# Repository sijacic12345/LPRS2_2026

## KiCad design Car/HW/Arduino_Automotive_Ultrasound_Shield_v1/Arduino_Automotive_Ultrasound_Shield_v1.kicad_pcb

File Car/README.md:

# 🏎️ ROS2 Robot Car

Robotski automobil baziran na **ROS2** platformi sa dualnom arhitekturom (SBC + MCU).

---

## 🏗️ Arhitektura sistema

Sistem koristi podelu poslova između Raspberry Pi 5 i Arduina radi maksimalne efikasnosti:

| Komponenta | Uloga | Opis |
| :--- | :--- | :--- |
| **Raspberry Pi 5** | **CPU (Master)** | Donosi odluke, obrađuje ROS2 čvorove i šalje instrukcije. |
| **Arduino Nano** | **Controller (Slave)** | Direktna kontrola BLDC motora, Servo motora i čitanje senzora. |

### 🛰️ Komunikacioni Protokol (`fw_pkgs.hpp`)
Komunikacija se vrši preko paketa definisanih u `fw_pkgs.hpp`. 
> [!CAUTION]
> **VAŽNO:** Ovaj fajl postoji na dve lokacije. Ako menjaš strukturu u jednom, **moraš** je promeniti u oba:
> 1. `FW/Arduino_Motoro_Controller` (za Arduino)
> 2. `ROS2/ackibot_ws/src/ackibot_node/src/` (za Raspberry Pi)

* **M2S (Master to Slave):** Komande sa Pi-ja ka Arduinu (motor, servo).
* **S2M (Slave to Master):** Telemetrija sa Arduina ka Pi-ju (senzori, status).

---

## 📂 Ključni Fajlovi

* **Firmware:** `FW/Arduino_Motor_Controller/Arduino_Motor_Controller.ino` (Učitati na Arduino)
* **ROS2 Node:** `ROS2/ackibot_ws/src/ackibot_node/src/fw_node.cpp` (Glavna logika instrukcija)

---

## 🚀 Procedura Pokretanja

Prati ove korake tačnim redosledom kako bi izbegao greške u komunikaciji:

1.  **Power On:** Uključi Raspberry Pi (Interni prekidač).
2.  **Access:** Poveži se na Pi putem **SSH**.
3.  **Scripts:** Pokreni skriptu za joypad
    ```bash
    cd ROS2/ackibot_ws/scripts
    ./mars_joys.sh
    ```
4.  **Controller:** Upali joypad kombinacijom tastera **RB + HOME**.
5.  **Run:** Pokreni glavni proces:
    ```bash
    ./ackibot_run_sbc.sh
    ```
6.  **Motors:** Na samom kraju uključi **eksterni prekidač** za motore.

---

## 📶 Troubleshooting (Wi-Fi Problemi)

Ako se Raspberry Pi ne vidi na mreži:
* Poveži PI na monitor i proveri IP adresu u konzoli.
* **Quick Fix:** Ako ne možeš da mu pristupiš, probaj da **pinguješ svoj PC sa Pi-ja**. To često natera ruter da prepozna uređaj i otvori rutu.

---

## 🛠️ Build Instructions
Detaljna uputstva za kompajliranje i build sistema možeš pronaći na:
👉 [GitHub Repository Build Guide](https://github.com/cxxx1828/ROS2-Robot-Car)

---

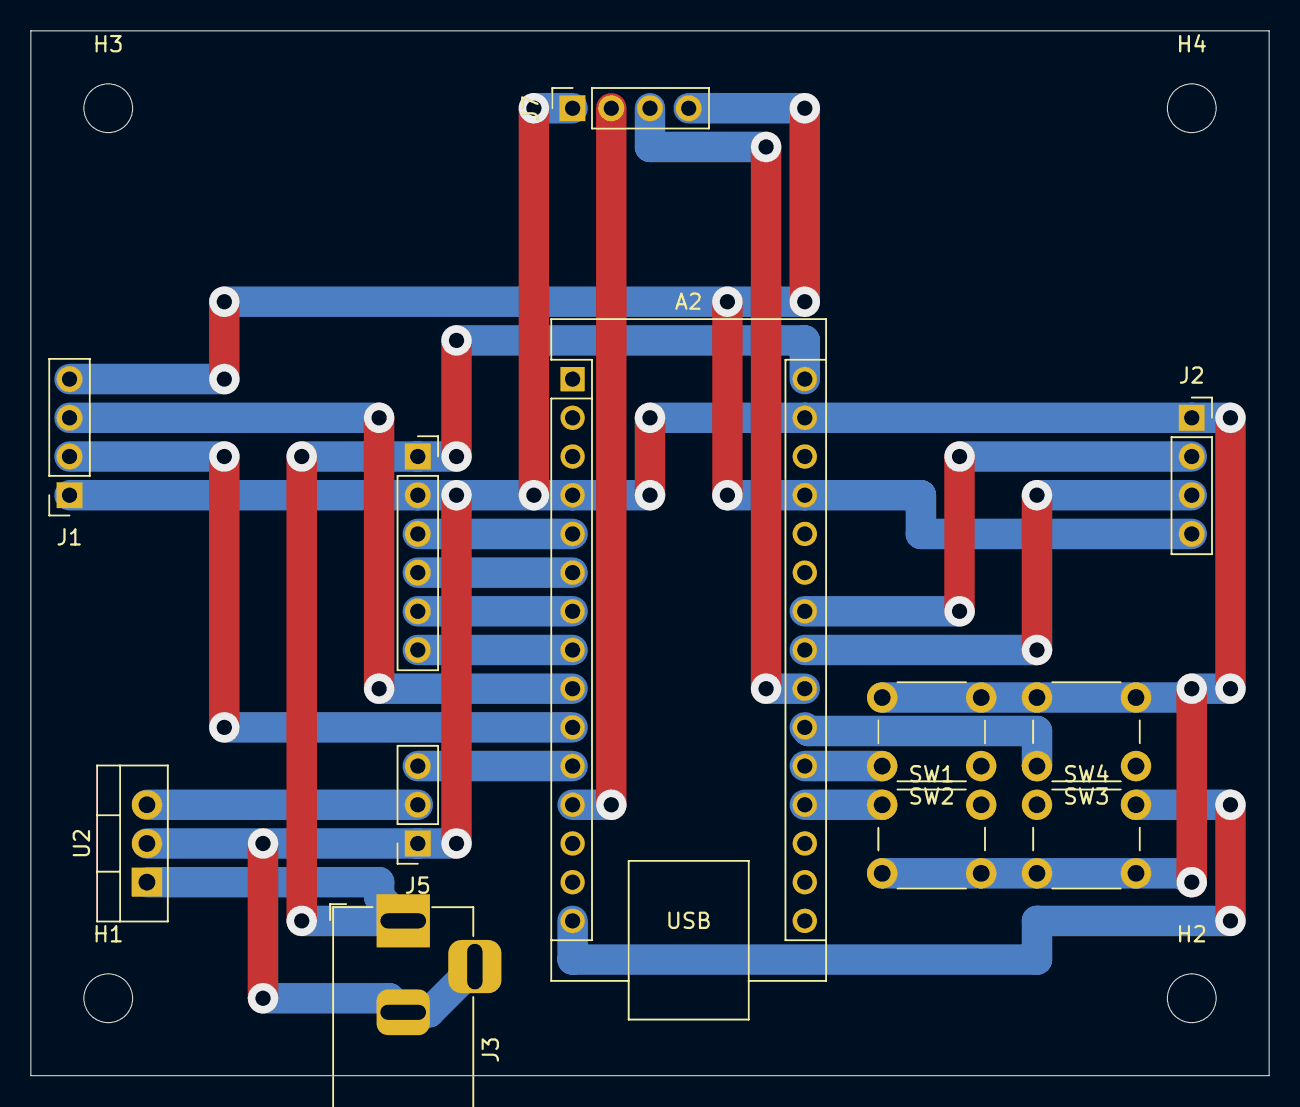
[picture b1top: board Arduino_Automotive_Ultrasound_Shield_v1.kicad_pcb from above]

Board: 2 copper layers, 81.3 x 68.6 mm, 16 parts (0 on the bottom side), 19 nets.

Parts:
A2: Arduino_Nano_Every; Arduino_Nano
H1, H2, H3, H4: M3; MountingHole_3.2mm_M3
J1, J2, J7: 1x4 2.54mm female; PinSocket_1x04_P2.54mm_Vertical
J3: Barrel_Jack_Switch; BarrelJack_Horizontal
J5: 1x3 2.54mm male; PinSocket_1x03_P2.54mm_Vertical
J6: 1x3 2.54mm male; PinSocket_1x06_P2.54mm_Vertical
SW1, SW2, SW3, SW4: SW_Push; SW_PUSH_6mm
U2: LM7805_TO220; TO-220-3_Vertical

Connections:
+5V: A2.27 (+5V), J1.4, J2.4, J7.4
+12V: A2.30 (VIN), J3.1, J6.1, U2.1 (VI)
/BREAK: A2.8 (D5), J6.6
/DIR: A2.7 (D4), J6.5
/ECHO_0: A2.12 (D9), J7.2
/ECHO_1: A2.24 (SCL/A5), J2.2
/ECHO_2: A2.10 (D7), J1.2
/FG: A2.5 (D2), J6.3
/PB0: A2.21 (A2), SW1.1
/PB1: A2.20 (A1), SW2.1
/PB2: A2.19 (A0), SW3.1
/PB3: A2.15 (MISO), SW4.1
/PWM: A2.6 (D3), J6.4
/STEER_PWM: A2.11 (D8), J5.3
/TRIG_0: A2.22 (A3), J7.3
/TRIG_1: A2.23 (SDA/A4), J2.3
/TRIG_2: A2.9 (D6), J1.3
GND: A2.4 (GND), A2.29 (GND), J1.1, J2.1, J3.2, J3.3, J5.1, J6.2, J7.1, SW1.2, SW2.2, SW3.2, SW4.2, U2.2 (GND)
Vdrive: J5.2, U2.3 (VO)

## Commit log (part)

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2026-03-24 Add Car
2026-03-29 Added work tree of all files
2026-03-29 deleted old files
2026-03-29 Updated work tree
2026-03-31 Temporarry braking distance change
2026-04-01 Test code 5cm distance
2026-04-07 Updated logic for braking, added adaptive braking distance
2026-04-21 fixed errors in fw_node.cpp
2026-04-21 fixed final_speed error
2026-04-21 trying to fix emergency braking logic not working
2026-04-21 changed lock logic from 1 second to until the user releases throttle
2026-04-21 fixed errors in typing
2026-04-21 fixing typing version 2
2026-04-21 fixed so console doesnt write velocity and angle inputs while emergency stop has blocked motors
2026-04-22 added flow for photo proccesing
2026-06-08 Added pictures and algo for lines
2026-06-10 Fixed line detection and added decision making algorithm
2026-06-25 Removed pictures
2026-06-25 Testing new speed restrictions for Automatic driving
2026-06-25 Added test scripts for line detection streaming to PC
2026-06-25 FIXED a mistake from last commit
2026-06-25 Fixed a bug on stream pipeline not working
2026-06-25 Fixed a bug on stream pipeline not working try 2
2026-06-25 fixed formating in camera pipeline
2026-06-25 pls make this the last change
2026-06-25 Another try to fix
2026-06-25 I think last try
2026-06-26 Trying to fix snow on stream
2026-06-26 Added pictures for testing
2026-06-26 Added timers to picture processing for tracking
2026-06-26 Changed line detection processing logic
2026-06-29 New linedetection logic test
2026-06-29 Fixed typos from last commit
